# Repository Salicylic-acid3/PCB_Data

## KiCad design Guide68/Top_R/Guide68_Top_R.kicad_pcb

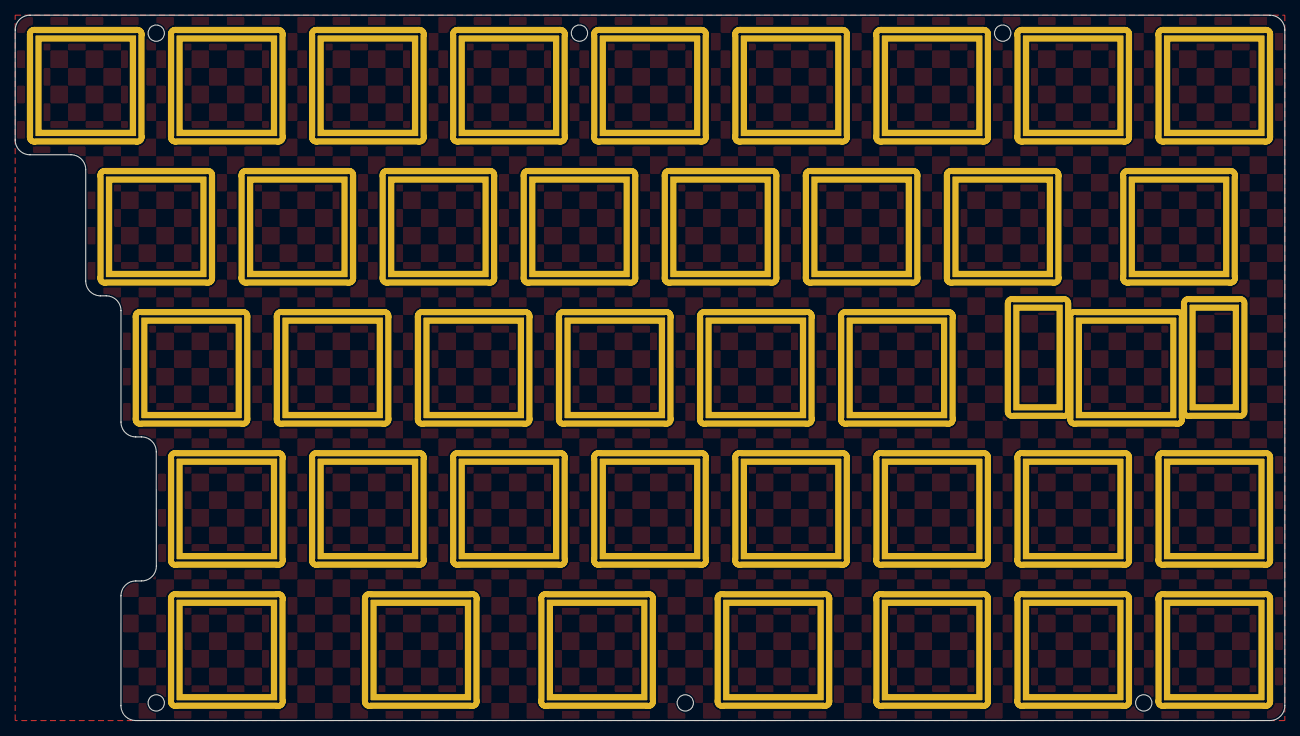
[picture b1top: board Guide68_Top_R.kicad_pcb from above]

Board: 2 copper layers, 171.5 x 95.2 mm, 45 parts (0 on the bottom side), 8 nets, no tracks yet.

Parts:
J4, J5, J13, J14, J15, J16: Conn_01x01; m2_Screw_Hole
SW30, SW31, SW32, SW33, SW34, SW35, SW36, SW37, SW38, SW39, SW40, SW41, SW42, SW43, SW44, SW45, SW46, SW47, SW48, SW49, SW50, SW51, SW52, SW53, SW54, SW55, SW56, SW57, SW58, SW59, SW60, SW62, SW63, SW64, SW65, SW66, SW67, SW68: SW_PUSH; SW_Hole_TH_1u
SW61: SW_PUSH; SW_Hole_TH_2.25u

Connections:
Col0: SW30.1, SW31.1, SW32.1, SW33.1, SW34.1
Col1: SW35.1, SW36.1, SW37.1, SW38.1, SW39.1
Col2: SW40.1, SW41.1, SW42.1, SW43.1
Col3: SW44.1, SW45.1, SW46.1, SW47.1, SW48.1
Col4: SW49.1, SW50.1, SW51.1, SW52.1, SW53.1
Col5: SW54.1, SW55.1, SW56.1, SW57.1, SW58.1
Col6: SW59.1, SW60.1, SW61.1, SW62.1, SW63.1
Col7: SW64.1, SW65.1, SW66.1, SW67.1, SW68.1
